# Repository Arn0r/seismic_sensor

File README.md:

<h1 align="center">Mantle</h1>

<p align="center" width="100%">
  
</p>

***

<p align="center">
  
&nbsp; &nbsp; &nbsp; &nbsp;
  
</p>

***

## SPECIFICATIONS

| Parameter | Value | 
| --- | --- |
| Dimensions | N/A × N/A mm |

***

## DIRECTORY STRUCTURE

    .
    ├─ Computations       # Misc calculations
    ├─ HTML               # HTML files for generated webpage
    ├─ Images             # Pictures and renders
    │
    ├─ kibot_resources    # External resources for KiBot
    │  ├─ colors          # Color theme for KiCad
    │  ├─ fonts           # Fonts used in the project
    │  ├─ scripts         # External scripts used with KiBot
    │  └─ templates       # Templates for KiBot generated reports
    │
    ├─ kibot_yaml         # KiBot YAML config files
    ├─ KiRI               # KiRI (PCB diff viewer) files
    │
    ├─ lib                # KiCad footprint and symbol libraries
    │  ├─ 3d_models       # Component 3D models
    │  ├─ lib_fp          # Footprint libraries
    │  └─ lib_sym         # Symbol libraries
    │
    ├─ Logos              # Logos
    │
    ├─ Manufacturing      # Assembly and fabrication documents
    │  ├─ Assembly        # Assembly documents (BoM, pos, notes)
    │  │
    │  └─ Fabrication     # Fabrication documents (ZIP, notes)
    │     ├─ Drill Tables # CSV drill tables
    │     └─ Gerbers      # Gerbers
    │
    ├─ Report             # Reports for ERC/DRC
    ├─ Schematic          # PDF of schematic
    ├─ Templates          # Title block templates
    ├─ Testing
    │  └─ Testpoints      # Testpoints tables      
    │
    └─ Variants           # Outputs for assembly variants

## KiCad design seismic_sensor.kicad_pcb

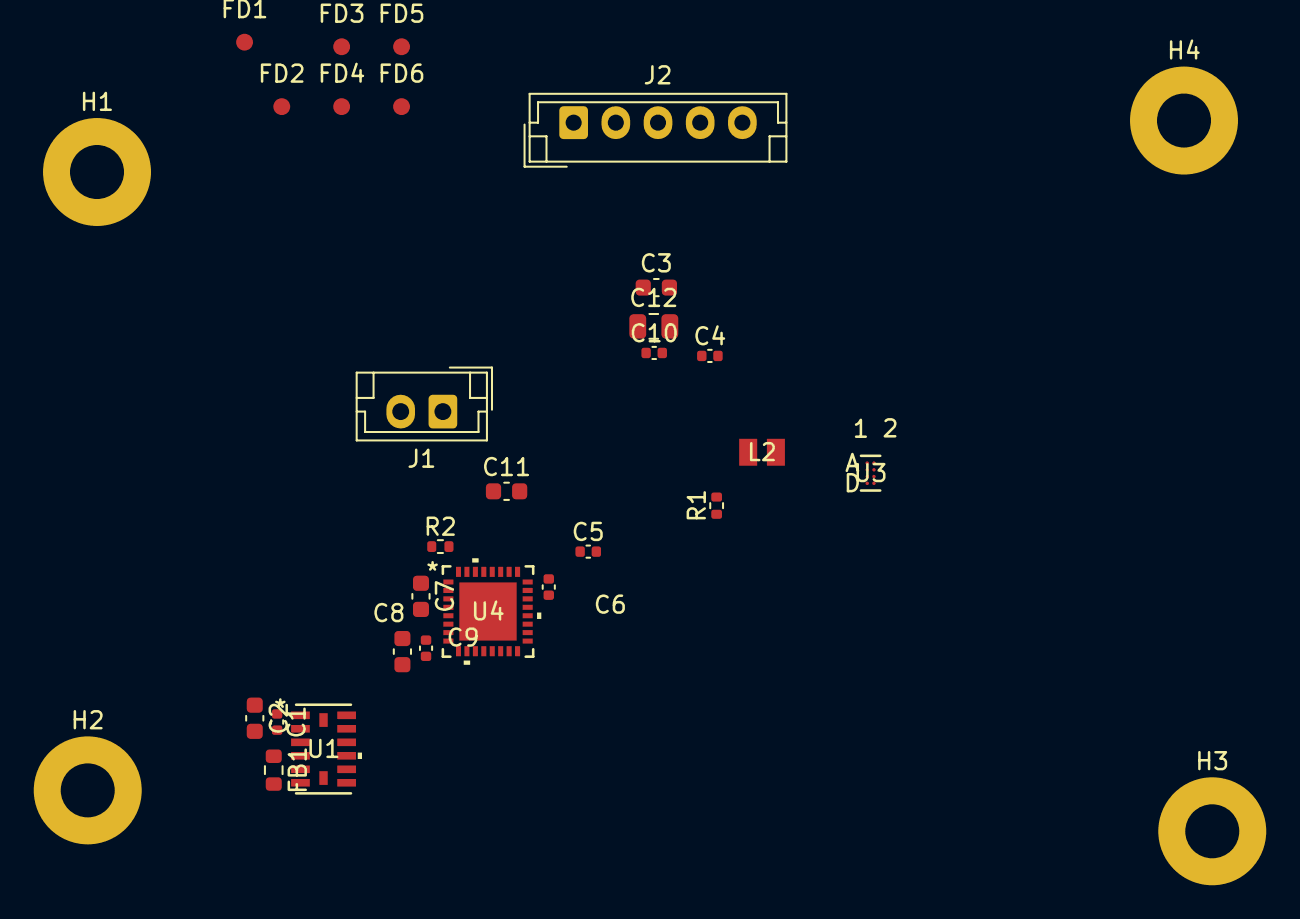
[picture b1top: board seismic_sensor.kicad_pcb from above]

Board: 6 copper layers, 31 parts (0 on the bottom side), 9 nets, no tracks yet.

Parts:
C1, C4, C5, C6, C9, C10: 0.1u; C_0402_1005Metric
C2, C3: 10u; C_0603_1608Metric
C7, C8: 1u; C_0603_1608Metric
C11: 22u; C_0603_1608Metric
C12: 47u; C_0805_2012Metric
FB1: FerriteBead; FB_0603_1608Metric
FD1, FD2, FD3, FD4, FD5, FD6: Fiducial; Fiducial_1mm_Mask2mm
H1, H2, H3, H4: M3; MountingHole_3.2mm_M3_Pad
J1: Conn_01x02; JST_EH_B2B-EH-A_1x02_P2.50mm_Vertical
J2: Conn_01x05; JST_EH_B5B-EH-A_1x05_P2.50mm_Vertical
L2: 1u; HTEK20161T-1R0MSR_CYN
R1, R2: 4k7; R_0402_1005Metric
U1: ADXL345BCCZ; LGA_CC-14-1_ADI
U3: TPS631012YBGR; DSBGA8-YBG_TEX
U4: STM32U031K8U6; UFQFPN-32_STM

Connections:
+3V3: C1.1, C2.1, C3.1, C4.1, C5.1, C6.1, C7.1, C8.1, C9.1, C10.1, C12.1, FB1.1, J2.5, R1.1, R2.1, U1.1 (VDD_I/O), U4.1 (VBAT), U4.9 (VDDA), U4.24 (VDD)
/Project Architecture/Connectors/NRST: J2.2, U4.7 (PF2)
/Project Architecture/Connectors/SCL: R1.2, U4.31 (PA10)
/Project Architecture/Connectors/SDA: R2.2, U4.32 (PA11)
/Project Architecture/IMU/CS*: U1.7 (*CS), U4.18 (PB0)
/Project Architecture/IMU/INT: U1.8 (INT1), U4.19 (PB1)
GND: C1.2, C2.2, C3.2, C4.2, C5.2, C6.2, C7.2, C8.2, C9.2, C10.2, C11.2, C12.2, H1.1, H2.1, H3.1, H4.1, J1.1, J2.1, U1.2 (GND), U1.4 (GND), U1.5 (GND), U4.8 (VSSA), U4.23 (VSS)
unnamed: FB1.2, U1.6 (VS)
VBUS: C11.1, J1.2

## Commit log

2026-01-23 Added CI Workflow
2026-01-23 updated project name
2026-01-23 Update Outputs
2026-01-23 cleanup
2026-02-03 First draft of the schematic
2026-02-12 Schematic work & cleanup
2026-05-16 updated structure
